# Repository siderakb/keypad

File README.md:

# Keypad

## [KP06](./KP06_keypad/)

## [KP08](./KP08_keypad/)

- [Gerber files](./KP08_keypad/gerber/)
- [Schematic](./KP08_keypad/schematic.pdf)

## [KP08Hub](./KP08Hub_keypad/)

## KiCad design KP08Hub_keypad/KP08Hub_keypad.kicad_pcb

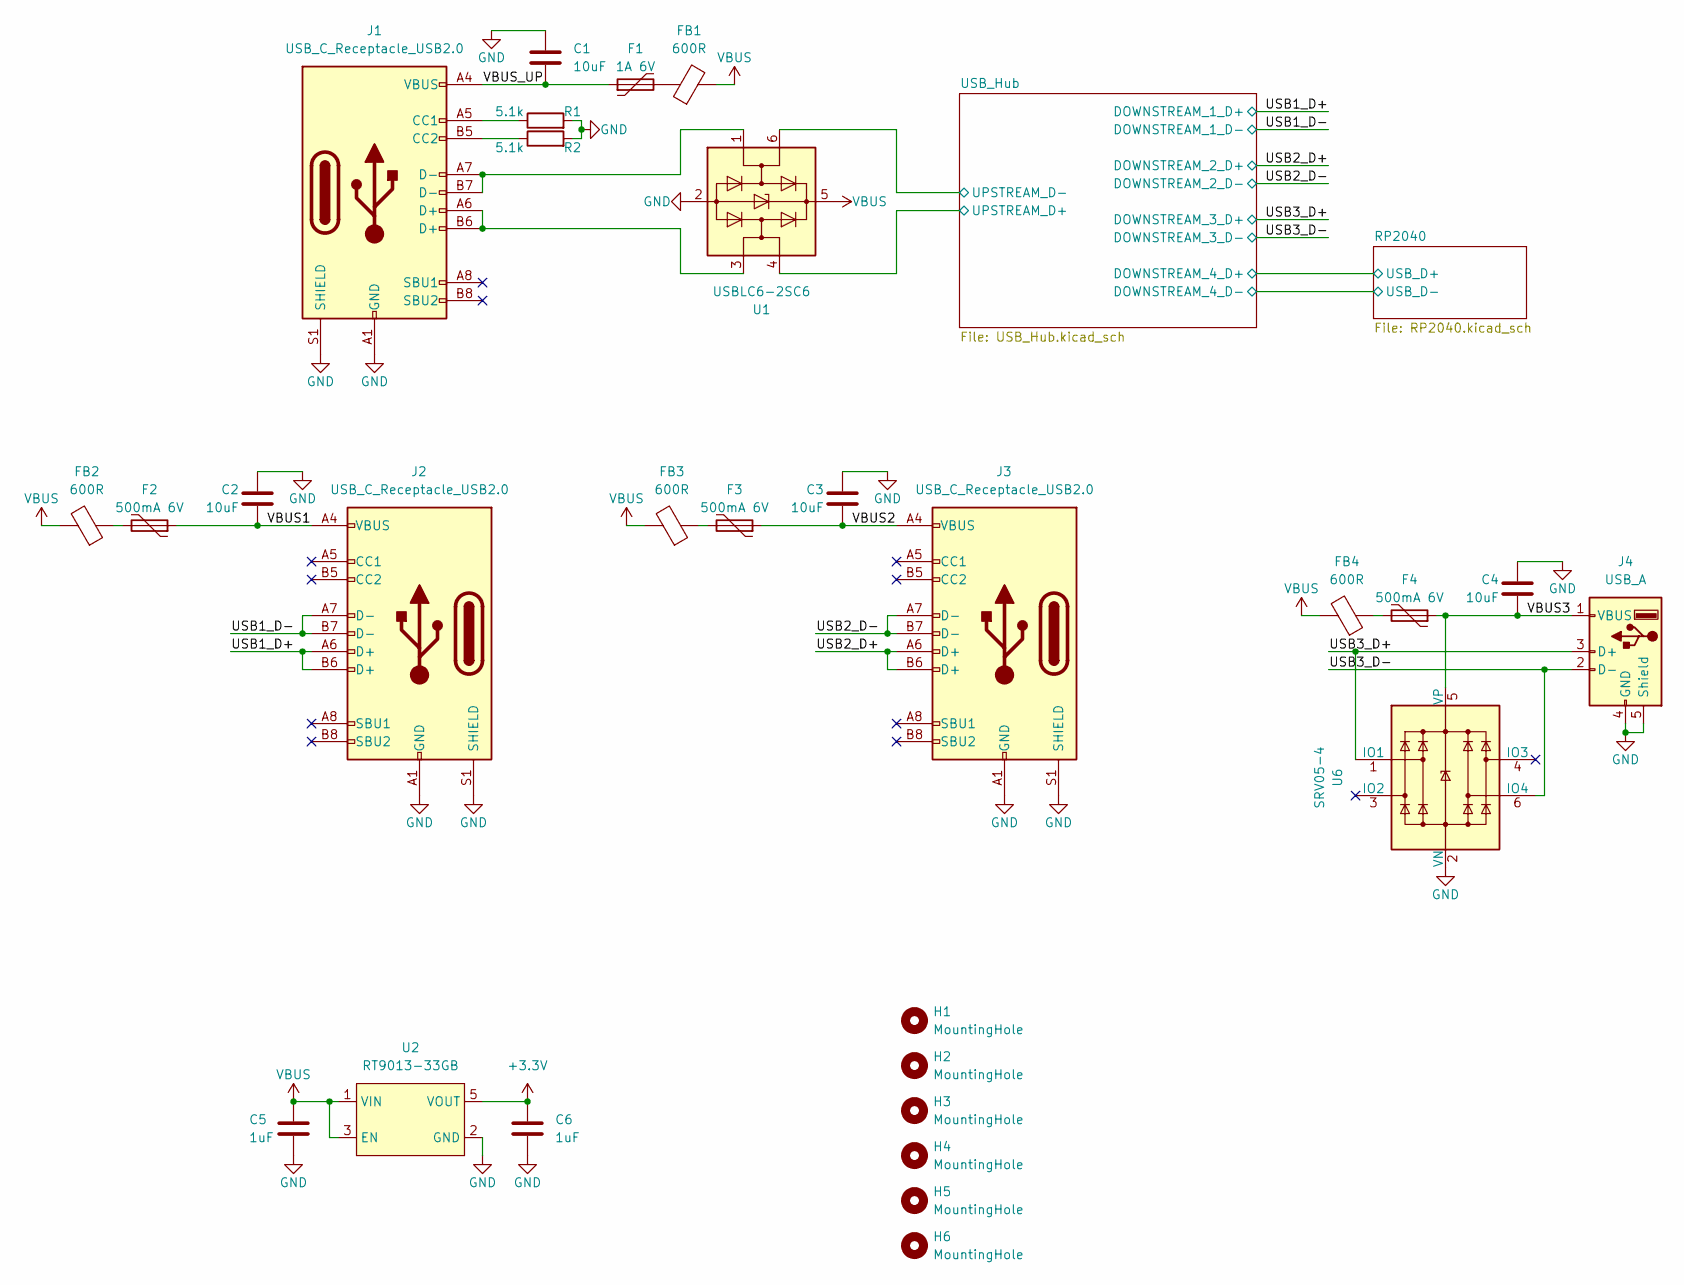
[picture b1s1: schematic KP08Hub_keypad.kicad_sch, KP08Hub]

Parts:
C1, C2, C3, C4: 10uF; C_0402_1005Metric; MFR. Part # CL05A106MQ5NUNC; JLCPCB Part # C15525
C5, C6: 1uF; C_0402_1005Metric; MFR. Part # CL05A105KA5NQNC; JLCPCB Part # C52923
F1: 1A 6V; Fuse_0805_2012Metric; MFR. Part # SMD0805-100; JLCPCB Part # C70061
F2, F3, F4: 500mA 6V; Fuse_0805_2012Metric; MFR. Part # SMD0805B050TF; JLCPCB Part # C269104
FB1, FB2, FB3, FB4: 600R; L_0805_2012Metric; MFR. Part # GZ2012D601TF; JLCPCB Part # C1017
H1, H2, H3, H4, H5, H6: MountingHole; MountingHole_2.2mm_M2_ISO7380
J1, J2, J3: USB_C_Receptacle_USB2.0; USB_C_Receptacle_HRO_TYPE-C-31-M-12; MFR. Part # TYPE-C-31-M-12; JLCPCB Part # C165948
J4: USB_A; USB_A_Molex_67643_Horizontal; MFR. Part # 902-131A1011D10100; JLCPCB Part # C2345
R1, R2: 5.1k; R_0402_1005Metric; MFR. Part # 0402WGF5101TCE; JLCPCB Part # C25905
U1: USBLC6-2SC6; SOT-23-6; MFR. Part # USBLC6-2SC6; JLCPCB Part # C2827654
U2: RT9013-33GB; SOT-23-5; MFR. Part # RT9013-33GB; JLCPCB Part # C47773
U6: SRV05-4; SOT-23-6; MFR. Part # SRV05-4-P-T7; JLCPCB Part # C85364

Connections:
+3.3V: C6.1, U2.5 (VOUT); also elsewhere on the board
/USB1_D+: J2.A6 (D+), J2.B6 (D+); also elsewhere on the board
/USB1_D-: J2.A7 (D-), J2.B7 (D-); also elsewhere on the board
/USB2_D+: J3.A6 (D+), J3.B6 (D+); also elsewhere on the board
/USB2_D-: J3.A7 (D-), J3.B7 (D-); also elsewhere on the board
/USB3_D+: J4.3 (D+), U6.1 (IO1); also elsewhere on the board
/USB3_D-: J4.2 (D-), U6.6 (IO4); also elsewhere on the board
/USB_Hub/UPSTREAM_D+: U1.4 (I/O2); also elsewhere on the board
/USB_Hub/UPSTREAM_D-: U1.6 (I/O1); also elsewhere on the board
/VBUS1: C2.2, F2.1, J2.A4 (VBUS), J2.A9 (VBUS), J2.B4 (VBUS), J2.B9 (VBUS)
/VBUS2: C3.2, F3.1, J3.A4 (VBUS), J3.A9 (VBUS), J3.B4 (VBUS), J3.B9 (VBUS)
/VBUS3: C4.2, F4.1, J4.1 (VBUS), U6.5 (VP)
/VBUS_UP: C1.2, F1.1, J1.A4 (VBUS), J1.A9 (VBUS), J1.B4 (VBUS), J1.B9 (VBUS)
GND: C1.1, C2.1, C3.1, C4.1, C5.2, C6.2, J1.A1 (GND), J1.A12 (GND), J1.B1 (GND), J1.B12 (GND), J1.S1 (SHIELD), J2.A1 (GND), J2.A12 (GND), J2.B1 (GND), J2.B12 (GND), J2.S1 (SHIELD), J3.A1 (GND), J3.A12 (GND), J3.B1 (GND), J3.B12 (GND), J3.S1 (SHIELD), J4.4 (GND), J4.5 (Shield), R1.2, R2.2, U1.2 (GND), U2.2 (GND), U6.2 (VN); also elsewhere on the board
unnamed: F1.2, FB1.1
unnamed: F2.2, FB2.1
unnamed: F3.2, FB3.1
unnamed: F4.2, FB4.1
unnamed: J1.A5 (CC1), R1.1
unnamed: J1.A6 (D+), J1.B6 (D+), U1.3 (I/O2)
unnamed: J1.A7 (D-), J1.B7 (D-), U1.1 (I/O1)
unnamed: J1.B5 (CC2), R2.1
VBUS: C5.1, FB1.2, FB2.2, FB3.2, FB4.2, U1.5 (VBUS), U2.1 (VIN), U2.3 (EN); also elsewhere on the board

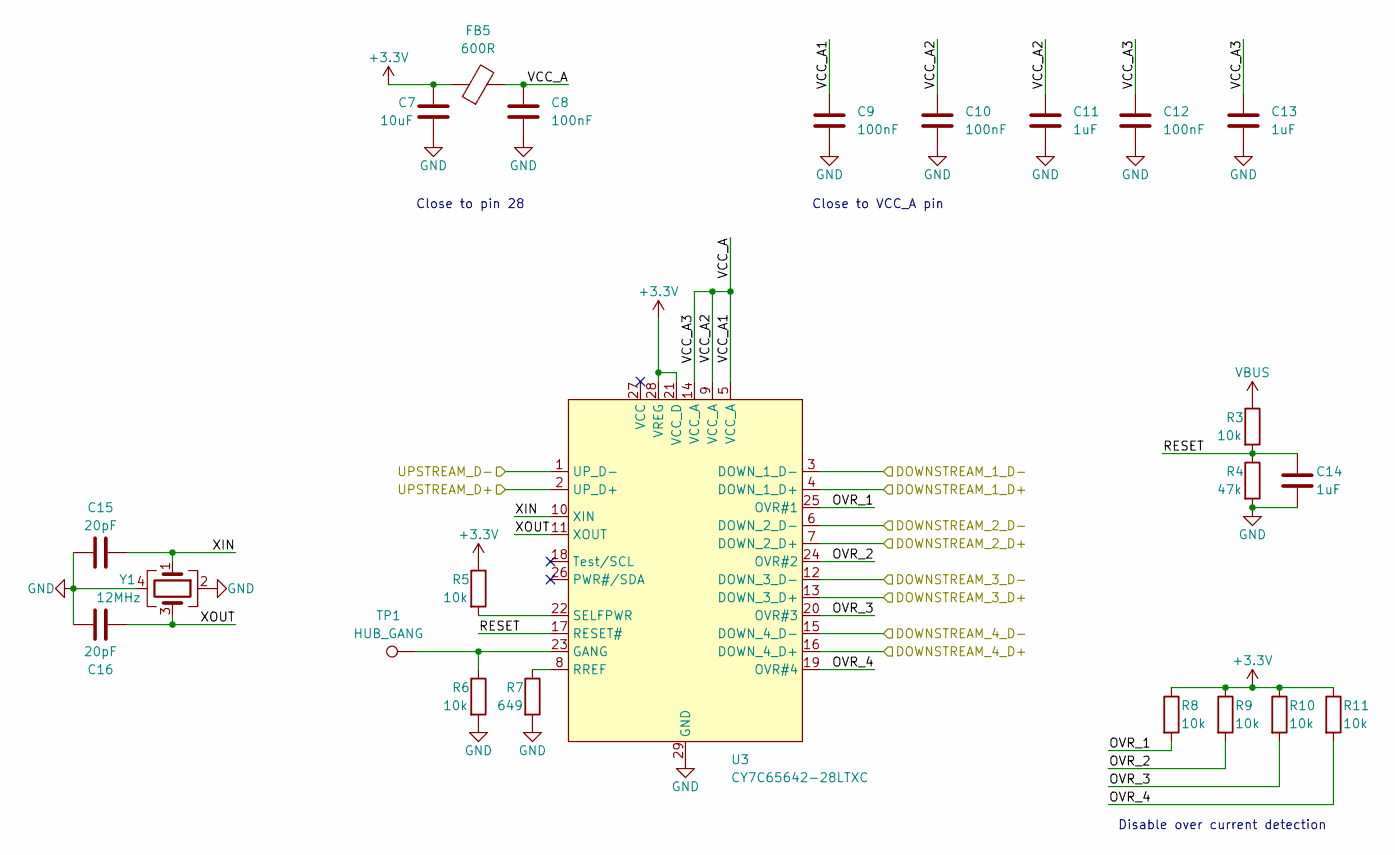
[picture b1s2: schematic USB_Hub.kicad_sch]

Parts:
C7: 10uF; C_0402_1005Metric; MFR. Part # CL05A106MQ5NUNC; JLCPCB Part # C15525
C8, C9, C10, C12: 100nF; C_0402_1005Metric; MFR. Part # CL05B104KO5NNNC; JLCPCB Part # C1525
C11, C13, C14: 1uF; C_0402_1005Metric; MFR. Part # CL05A105KA5NQNC; JLCPCB Part # C52923
C15, C16: 20pF; C_0402_1005Metric; MFR. Part # 0402CG200J500NT; JLCPCB Part # C1554
FB5: 600R; L_0805_2012Metric; MFR. Part # GZ2012D601TF; JLCPCB Part # C1017
R3, R5, R6, R8, R9, R10, R11: 10k; R_0402_1005Metric; MFR. Part # 0402WGF1002TCE; JLCPCB Part # C25744
R4: 47k; R_0402_1005Metric; MFR. Part # 0402WGF4702TCE; JLCPCB Part # C25792
R7: 649; R_0402_1005Metric; MFR. Part # 0402WGF6490TCE; JLCPCB Part # C82294
TP1: HUB_GANG; TestPoint_Pad_D2.0mm
U3: CY7C65642-28LTXC; QFN-28-1EP_5x5mm_P0.5mm_EP3.35x3.35mm_ThermalVias; MFR. Part # CY7C65642-28LTXC; JLCPCB Part # C2759934
Y1: 12MHz; Crystal_SMD_3225-4Pin_3.2x2.5mm; MFR. Part # X322512MSB4SI; JLCPCB Part # C9002

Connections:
+3.3V: C7.1, FB5.1, R5.1, R8.1, R9.1, R10.1, R11.1, U3.21 (VCC_D), U3.28 (VREG); also elsewhere on the board
/RP2040/USB_D+: U3.16 (DOWN_4_D+); also elsewhere on the board
/RP2040/USB_D-: U3.15 (DOWN_4_D-); also elsewhere on the board
/USB1_D+: U3.4 (DOWN_1_D+); also elsewhere on the board
/USB1_D-: U3.3 (DOWN_1_D-); also elsewhere on the board
/USB2_D+: U3.7 (DOWN_2_D+); also elsewhere on the board
/USB2_D-: U3.6 (DOWN_2_D-); also elsewhere on the board
/USB3_D+: U3.13 (DOWN_3_D+); also elsewhere on the board
/USB3_D-: U3.12 (DOWN_3_D-); also elsewhere on the board
/USB_Hub/OVR_1: R8.2, U3.25 (OVR#1)
/USB_Hub/OVR_2: R9.2, U3.24 (OVR#2)
/USB_Hub/OVR_3: R10.2, U3.20 (OVR#3)
/USB_Hub/OVR_4: R11.2, U3.19 (OVR#4)
/USB_Hub/RESET: C14.1, R3.2, R4.1, U3.17 (RESET#)
/USB_Hub/UPSTREAM_D+: U3.2 (UP_D+); also elsewhere on the board
/USB_Hub/UPSTREAM_D-: U3.1 (UP_D-); also elsewhere on the board
/USB_Hub/VCC_A: C8.1, C9.1, C10.1, C11.1, C12.1, C13.1, FB5.2, U3.5 (VCC_A), U3.9 (VCC_A), U3.14 (VCC_A)
/USB_Hub/XIN: C15.2, U3.10 (XIN), Y1.1
/USB_Hub/XOUT: C16.2, U3.11 (XOUT), Y1.3
GND: C7.2, C8.2, C9.2, C10.2, C11.2, C12.2, C13.2, C14.2, C15.1, C16.1, R4.2, R6.2, R7.2, U3.29 (GND), Y1.2, Y1.4; also elsewhere on the board
unnamed: R5.2, U3.22 (SELFPWR)
unnamed: R6.1, TP1.1, U3.23 (GANG)
unnamed: R7.1, U3.8 (RREF)
VBUS: R3.1; also elsewhere on the board

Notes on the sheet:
Disable over current detection
Close to pin 28
Close to VCC_A pin

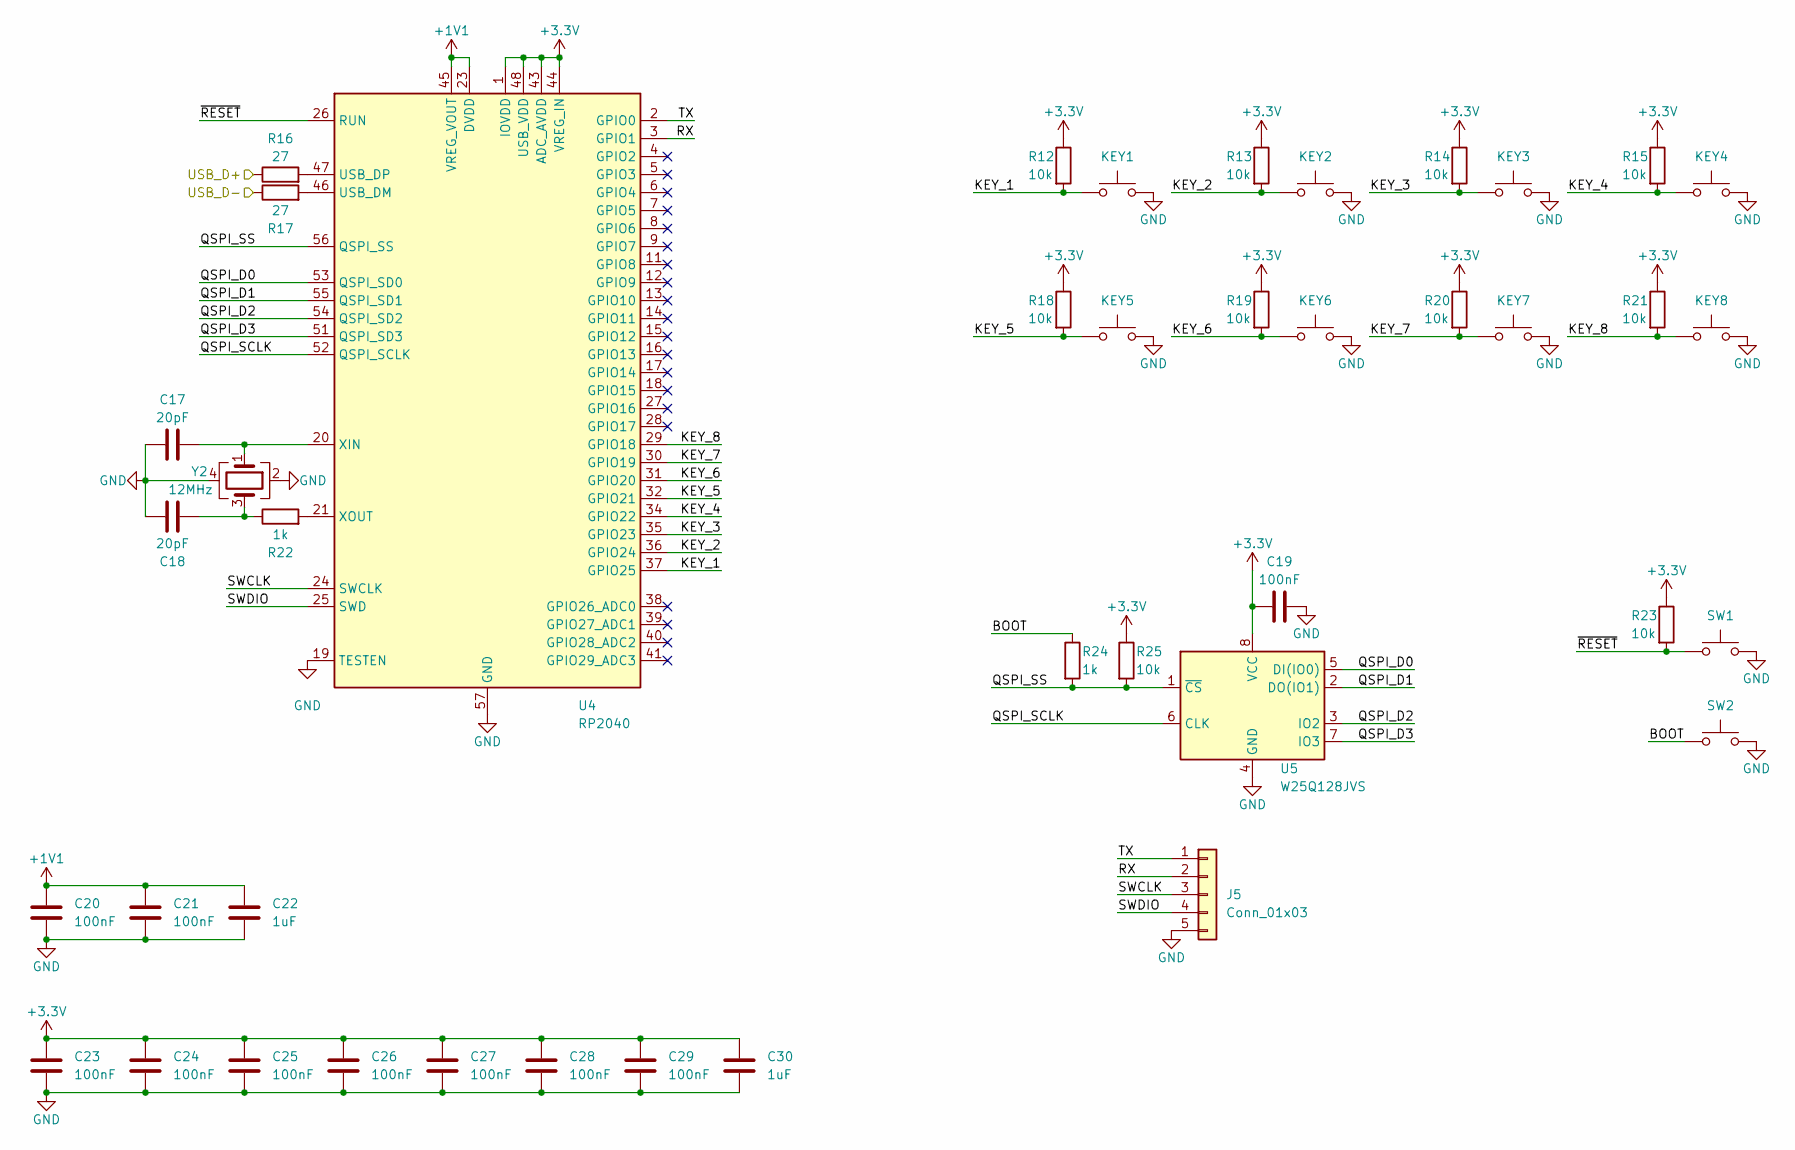
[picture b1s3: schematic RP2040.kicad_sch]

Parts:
C17, C18: 20pF; C_0402_1005Metric; MFR. Part # 0402CG200J500NT; JLCPCB Part # C1554
C19, C20, C21, C23, C24, C25, C26, C27, C28, C29: 100nF; C_0402_1005Metric; MFR. Part # CL05B104KO5NNNC; JLCPCB Part # C1525
C22, C30: 1uF; C_0402_1005Metric; MFR. Part # CL05A105KA5NQNC; JLCPCB Part # C52923
J5: Conn_01x03; PinHeader_1x05_P2.54mm_Vertical
KEY1, KEY2, KEY3, KEY4, KEY5, KEY6, KEY7, KEY8: SW_Push; MX_switch_THT_hotswap_A
R12, R13, R14, R15, R18, R19, R20, R21, R23, R25: 10k; R_0402_1005Metric; MFR. Part # 0402WGF1002TCE; JLCPCB Part # C25744
R16, R17: 27; R_0603_1608Metric; MFR. Part # 0603WAF270JT5E; JLCPCB Part # C25190
R22, R24: 1k; R_0402_1005Metric; MFR. Part # 0402WGF1001TCE; JLCPCB Part # C11702
SW1: RESET; SW_SPST_TL3342; MFR. Part # TS-1187A-B-A-B; JLCPCB Part # C318884
SW2: BOOT; SW_SPST_TL3342; MFR. Part # TS-1187A-B-A-B; JLCPCB Part # C318884
U4: RP2040; QFN-56-1EP_7x7mm_P0.4mm_EP3.2x3.2mm; MFR. Part # RP2040; JLCPCB Part # C2040
U5: W25Q128JVS; SOIC-8_5.23x5.23mm_P1.27mm; MFR. Part # W25Q128JVSIQ; JLCPCB Part # C97521
Y2: 12MHz; Crystal_SMD_3225-4Pin_3.2x2.5mm; MFR. Part # X322512MSB4SI; JLCPCB Part # C9002

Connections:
+1V1: C20.1, C21.1, C22.1, U4.23 (DVDD), U4.45 (VREG_VOUT), U4.50 (DVDD)
+3.3V: C19.1, C23.1, C24.1, C25.1, C26.1, C27.1, C28.1, C29.1, C30.1, R12.1, R13.1, R14.1, R15.1, R18.1, R19.1, R20.1, R21.1, R23.1, R25.1, U4.1 (IOVDD), U4.10 (IOVDD), U4.22 (IOVDD), U4.33 (IOVDD), U4.42 (IOVDD), U4.43 (ADC_AVDD), U4.44 (VREG_IN), U4.48 (USB_VDD), U4.49 (IOVDD), U5.8 (VCC); also elsewhere on the board
/RP2040/BOOT: R24.1, SW2.1
/RP2040/KEY_1: KEY1.1, R12.2, U4.37 (GPIO25)
/RP2040/KEY_2: KEY2.1, R13.2, U4.36 (GPIO24)
/RP2040/KEY_3: KEY3.1, R14.2, U4.35 (GPIO23)
/RP2040/KEY_4: KEY4.1, R15.2, U4.34 (GPIO22)
/RP2040/KEY_5: KEY5.1, R18.2, U4.32 (GPIO21)
/RP2040/KEY_6: KEY6.1, R19.2, U4.31 (GPIO20)
/RP2040/KEY_7: KEY7.1, R20.2, U4.30 (GPIO19)
/RP2040/KEY_8: KEY8.1, R21.2, U4.29 (GPIO18)
/RP2040/QSPI_D0: U4.53 (QSPI_SD0), U5.5 (DI(IO0))
/RP2040/QSPI_D1: U4.55 (QSPI_SD1), U5.2 (DO(IO1))
/RP2040/QSPI_D2: U4.54 (QSPI_SD2), U5.3 (IO2)
/RP2040/QSPI_D3: U4.51 (QSPI_SD3), U5.7 (IO3)
/RP2040/QSPI_SCLK: U4.52 (QSPI_SCLK), U5.6 (CLK)
/RP2040/QSPI_SS: R24.2, R25.2, U4.56 (QSPI_SS), U5.1 (~CS)
/RP2040/RX: J5.2, U4.3 (GPIO1)
/RP2040/SWCLK: J5.3, U4.24 (SWCLK)
/RP2040/SWDIO: J5.4, U4.25 (SWD)
/RP2040/TX: J5.1, U4.2 (GPIO0)
/RP2040/USB_D+: R16.1; also elsewhere on the board
/RP2040/USB_D-: R17.1; also elsewhere on the board
/RP2040/~RESET: R23.2, SW1.1, U4.26 (RUN)
GND: C17.1, C18.1, C19.2, C20.2, C21.2, C22.2, C23.2, C24.2, C25.2, C26.2, C27.2, C28.2, C29.2, C30.2, J5.5, KEY1.2, KEY2.2, KEY3.2, KEY4.2, KEY5.2, KEY6.2, KEY7.2, KEY8.2, SW1.2, SW2.2, U4.19 (TESTEN), U4.57 (GND), U5.4 (GND), Y2.2, Y2.4; also elsewhere on the board
unnamed: C17.2, U4.20 (XIN), Y2.1
unnamed: C18.2, R22.1, Y2.3
unnamed: R16.2, U4.47 (USB_DP)
unnamed: R17.2, U4.46 (USB_DM)
unnamed: R22.2, U4.21 (XOUT)

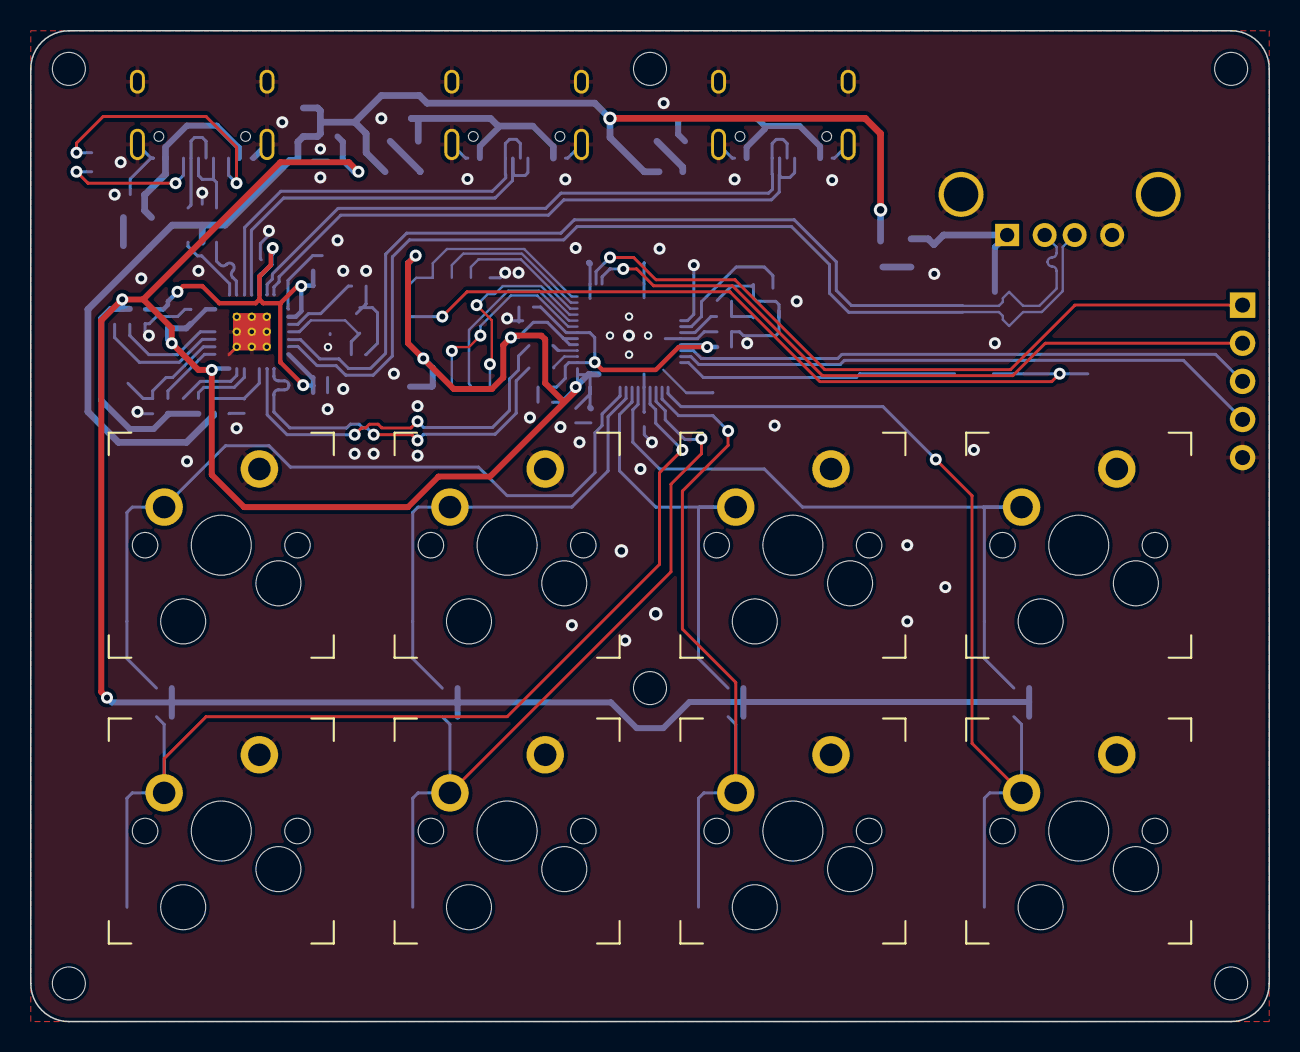
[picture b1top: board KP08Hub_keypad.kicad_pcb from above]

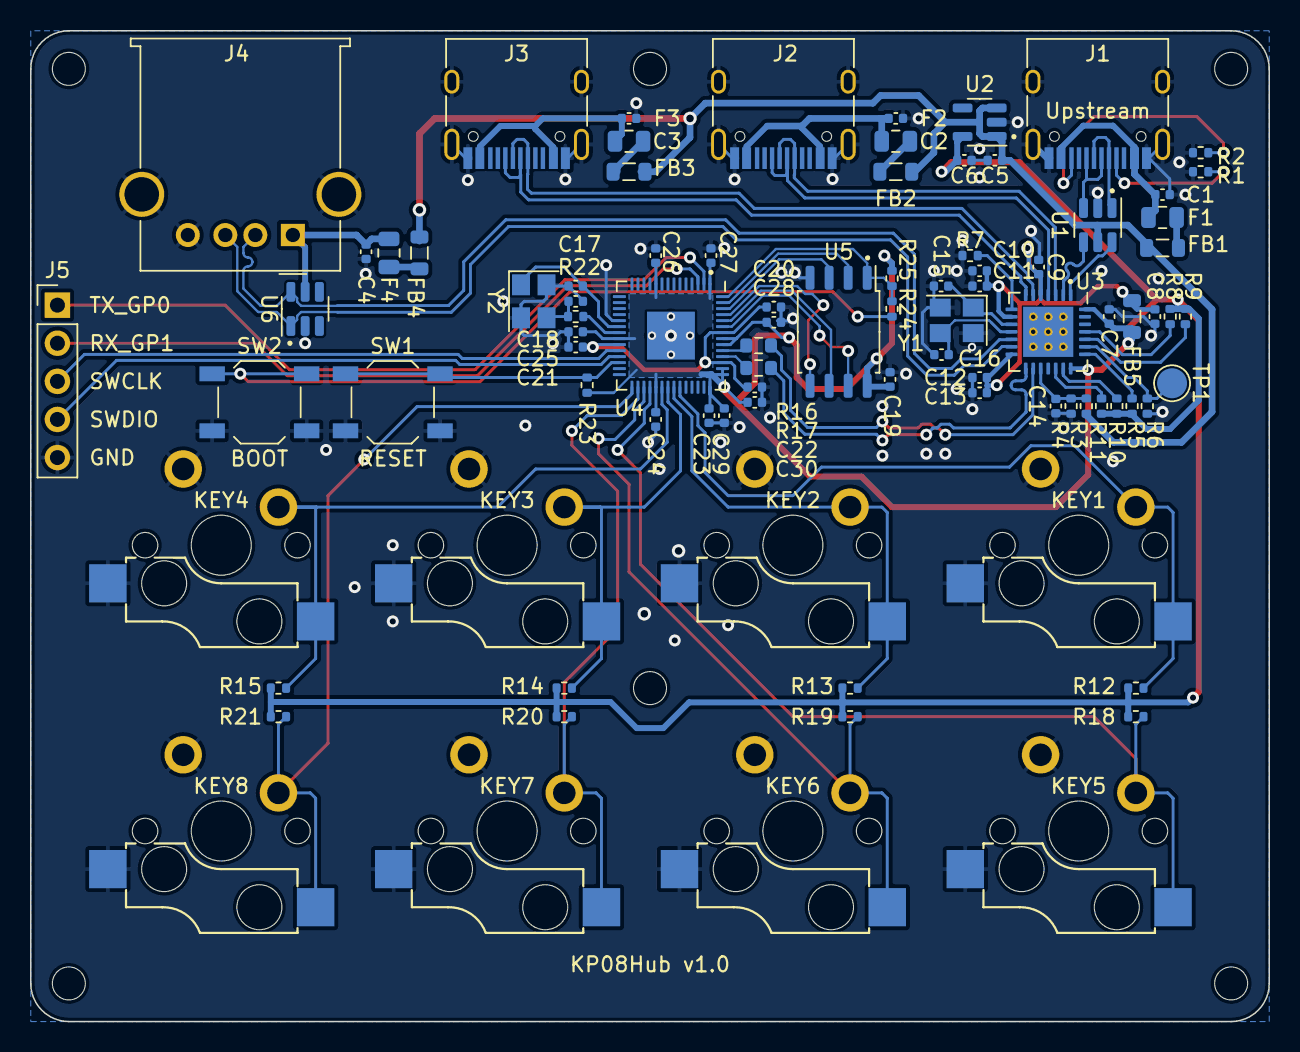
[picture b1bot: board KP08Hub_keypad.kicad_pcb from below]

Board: 2 copper layers, 82.6 x 66.0 mm, 94 parts (80 on the bottom side), 62 nets.

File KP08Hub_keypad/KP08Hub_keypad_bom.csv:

Comment,Designator,Footprint,JLCPCB Part #
"10uF","C1,C2,C3,C4,C7","Capacitor_SMD:C_0402_1005Metric","C15525"
"20pF","C15,C16,C17,C18","Capacitor_SMD:C_0402_1005Metric","C1554"
"1uF","C5,C6,C11,C13,C14,C22,C30","Capacitor_SMD:C_0402_1005Metric","C52923"
"100nF","C8,C9,C10,C12,C19,C20,C21,C23,C24,C25,C26,C27,C28,C29","Capacitor_SMD:C_0402_1005Metric","C1525"
"1A 6V","F1","Fuse:Fuse_0805_2012Metric","C70061"
"500mA 6V","F2,F3,F4","Fuse:Fuse_0805_2012Metric","C269104"
"600R","FB1,FB2,FB3,FB4,FB5","Inductor_SMD:L_0805_2012Metric","C1017"
"USB_C_Receptacle_USB2.0","J1,J2,J3","Connector_USB:USB_C_Receptacle_HRO_TYPE-C-31-M-12","C165948"
"USB_A","J4","Connector_USB:USB_A_Molex_67643_Horizontal","C2345"
"Conn_01x03","J5","Connector_PinHeader_2.54mm:PinHeader_1x05_P2.54mm_Vertical",""
"SW_Push","KEY1,KEY2,KEY3,KEY4,KEY5,KEY6,KEY7,KEY8","key-switches:MX_switch_THT_hotswap_A",""
"5.1k","R1,R2","Resistor_SMD:R_0402_1005Metric","C25905"
"27","R16,R17","Resistor_SMD:R_0603_1608Metric","C25190"
"1k","R22,R24","Resistor_SMD:R_0402_1005Metric","C11702"
"10k","R3,R5,R6,R8,R9,R10,R11,R12,R13,R14,R15,R18,R19,R20,R21,R23,R25","Resistor_SMD:R_0402_1005Metric","C25744"
"47k","R4","Resistor_SMD:R_0402_1005Metric","C25792"
"649","R7","Resistor_SMD:R_0402_1005Metric","C82294"
"RESET","SW1","Button_Switch_SMD:SW_SPST_TL3342","C318884"
"BOOT","SW2","Button_Switch_SMD:SW_SPST_TL3342","C318884"
"HUB_GANG","TP1","TestPoint:TestPoint_Pad_D2.0mm",""
"USBLC6-2SC6","U1","Package_TO_SOT_SMD:SOT-23-6","C2827654"
"RT9013-33GB","U2","Package_TO_SOT_SMD:SOT-23-5","C47773"
"CY7C65642-28LTXC","U3","Package_DFN_QFN:QFN-28-1EP_5x5mm_P0.5mm_EP3.35x3.35mm_ThermalVias","C2759934"
"RP2040","U4","Package_DFN_QFN:QFN-56-1EP_7x7mm_P0.4mm_EP3.2x3.2mm","C2040"
"W25Q128JVS","U5","Package_SO:SOIC-8_5.23x5.23mm_P1.27mm","C97521"
"SRV05-4","U6","Package_TO_SOT_SMD:SOT-23-6","C85364"
"12MHz","Y1,Y2","Crystal:Crystal_SMD_3225-4Pin_3.2x2.5mm","C9002"

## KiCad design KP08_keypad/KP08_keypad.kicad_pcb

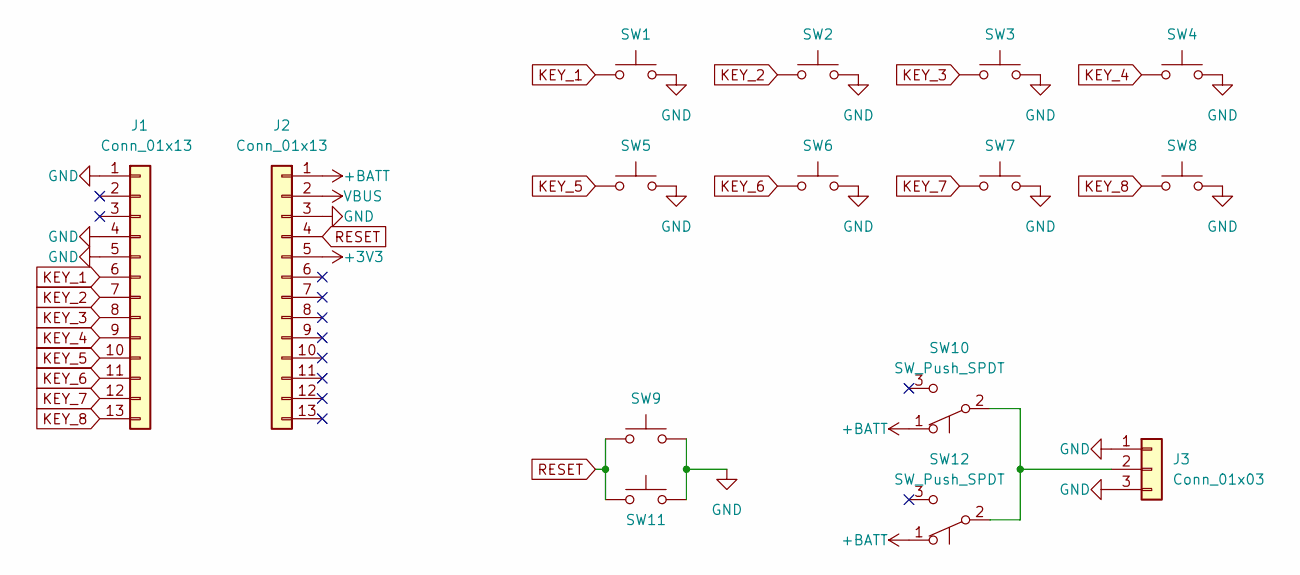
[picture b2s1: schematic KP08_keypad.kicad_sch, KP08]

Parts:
J1, J2: Conn_01x13; PinSocket_1x13_P2.54mm_Vertical
J3: Conn_01x03; JST_PH_B3B-PH-K_1x03_P2.00mm_Vertical
SW1, SW2, SW3, SW4, SW5, SW6, SW7, SW8: SW_Push; MX_switch_Gateron_hotswap_double_sided_A
SW9, SW11: SW_Push; SW_Push_1P1T_NO_6x6mm_H9.5mm
SW10, SW12: SW_Push_SPDT; SW_SPDT_PCM12

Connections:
+3V3: J2.5
+BATT: J2.1, SW10.1 (A), SW12.1 (A)
GND: J1.1, J1.4, J1.5, J2.3, J3.1, J3.3, SW1.2, SW2.2, SW3.2, SW4.2, SW5.2, SW6.2, SW7.2, SW8.2, SW9.2, SW11.2
KEY_1: J1.6, SW1.1
KEY_2: J1.7, SW2.1
KEY_3: J1.8, SW3.1
KEY_4: J1.9, SW4.1
KEY_5: J1.10, SW5.1
KEY_6: J1.11, SW6.1
KEY_7: J1.12, SW7.1
KEY_8: J1.13, SW8.1
unnamed: J3.2, SW10.2 (B), SW12.2 (B)
RESET: J2.4, SW9.1, SW11.1
VBUS: J2.2

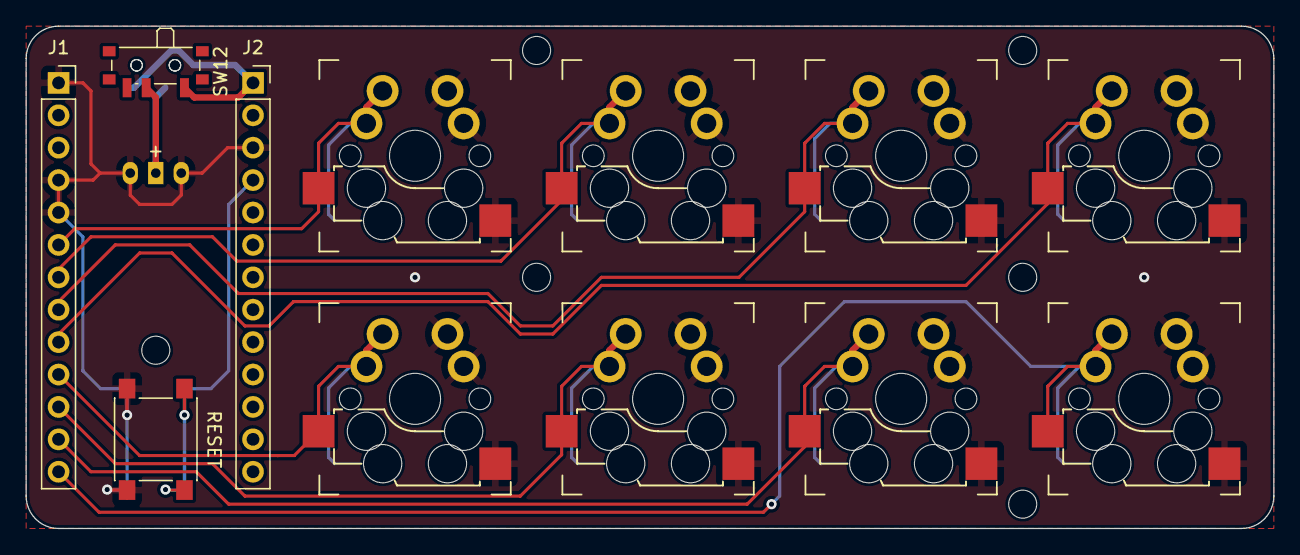
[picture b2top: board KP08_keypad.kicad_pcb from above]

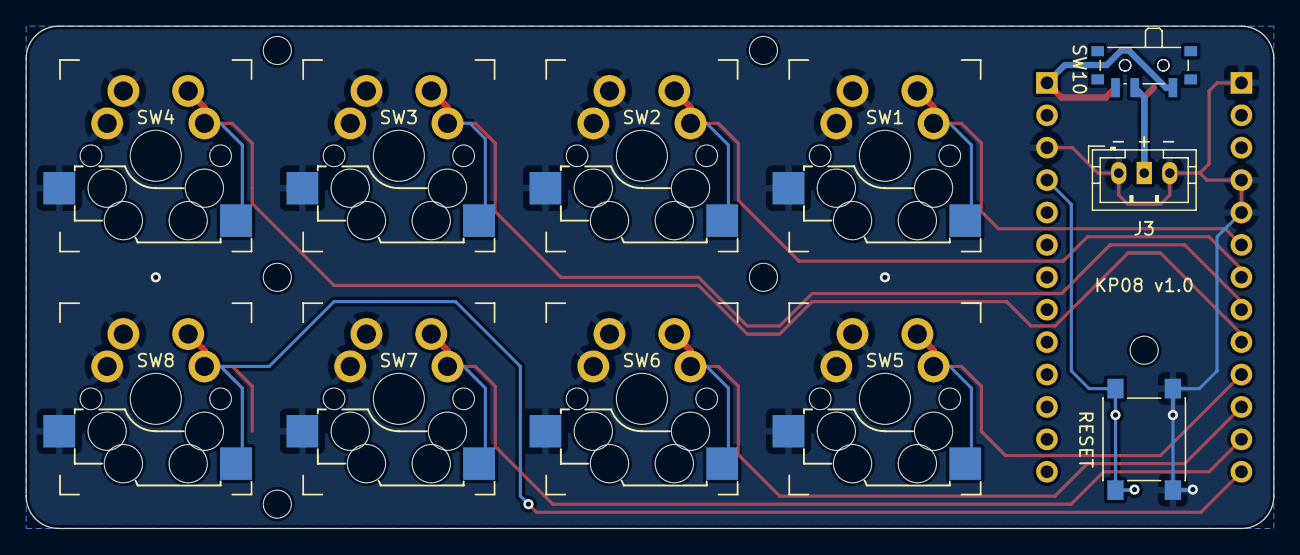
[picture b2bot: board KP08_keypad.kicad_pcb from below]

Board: 2 copper layers, 97.8 x 39.4 mm, 15 parts (3 on the bottom side), 12 nets.

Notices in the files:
KP06_keypad/KP06_keypad.kicad_pcb:
MIT License, Open source hardware
